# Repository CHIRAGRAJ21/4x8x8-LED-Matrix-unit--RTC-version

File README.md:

# 4x8x8-LED-Matrix-Unit (RTC version)
 A wholly designed KiCad based project featuring a 4x8x8 LED Matrix unit, which for this particular variation is developed to function as a real time clock; hold four 8x8 LED matrix displays controlled by an Arduino Pro mini. The board also includes two push buttons to which you can assign arbitrary functions. This board also features a connector for USB to TTL Serial Adapter Module for Arduino Mini Port USB to Serial Interface Module CYT1007 and a connector for DS3231 IIC Precision RTC, such that every time arduino need not to be detached from the board for uploading of a new program or updating the former employing an external bridging device.

# FINISHED and ASSEMBLED PCB

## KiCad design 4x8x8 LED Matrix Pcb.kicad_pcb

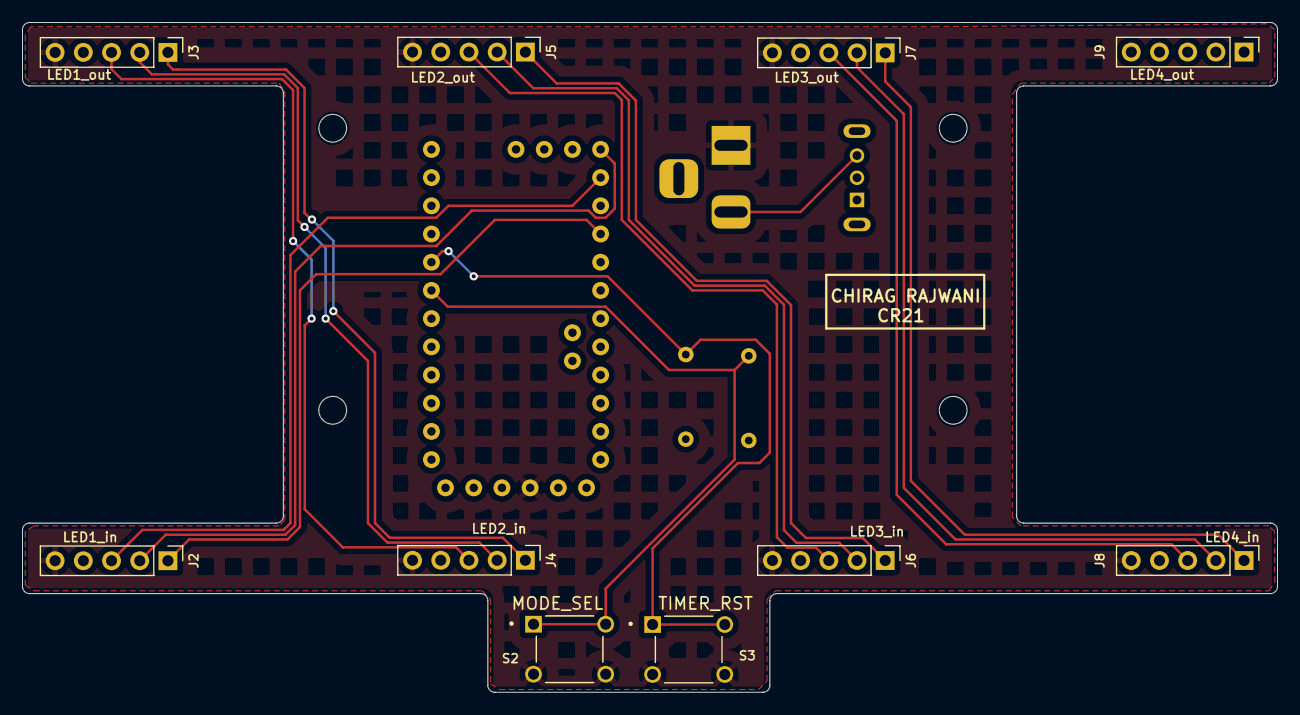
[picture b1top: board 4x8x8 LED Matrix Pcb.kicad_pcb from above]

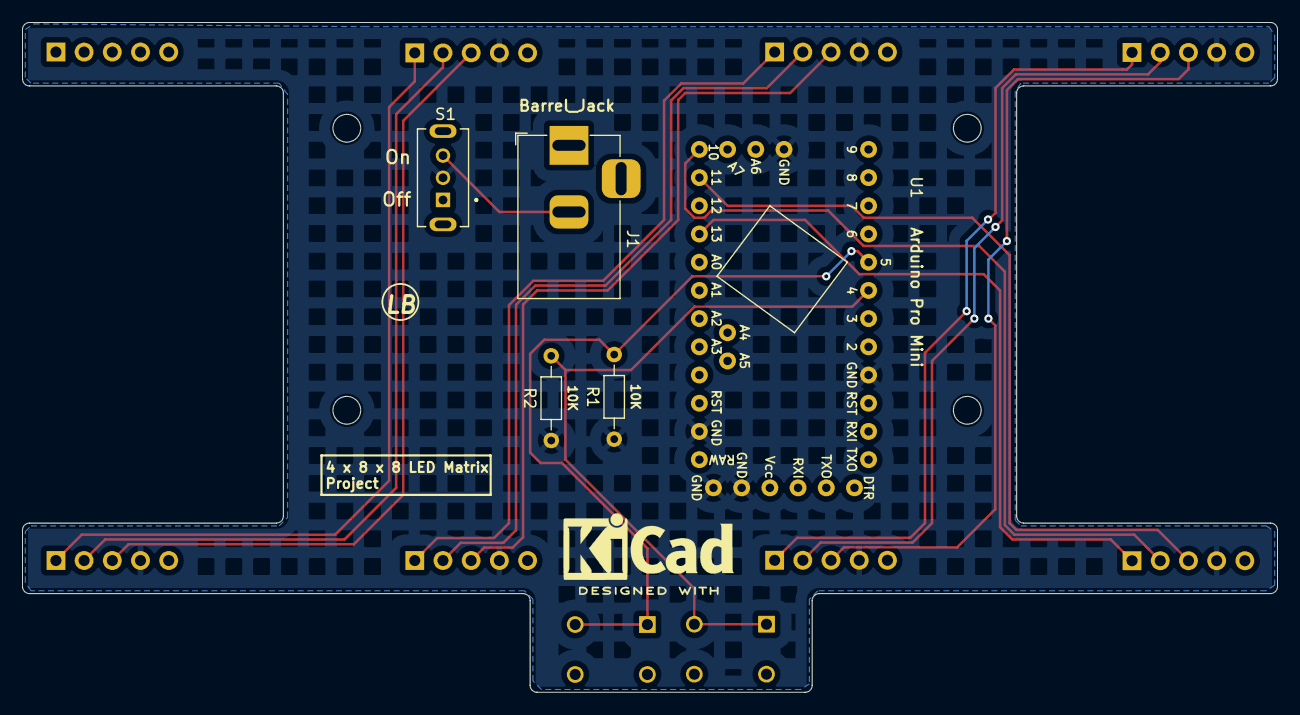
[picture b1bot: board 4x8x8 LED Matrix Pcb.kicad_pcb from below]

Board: 2 copper layers, 113.0 x 60.3 mm, 19 parts (5 on the bottom side), 17 nets.

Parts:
H1, H2, H3, H4: MountingHole; MountingHole_2.5mm
J1: Barrel_Jack; BarrelJack_Horizontal
J2: LED1_in; PinHeader_1x05_P2.54mm_Vertical
J3: LED1_out; PinHeader_1x05_P2.54mm_Vertical
J4: LED2_in; PinHeader_1x05_P2.54mm_Vertical
J5: LED2_out; PinHeader_1x05_P2.54mm_Vertical
J6: LED3_in; PinHeader_1x05_P2.54mm_Vertical
J7: LED3_out; PinHeader_1x05_P2.54mm_Vertical
J8: LED4_in; PinHeader_1x05_P2.54mm_Vertical
J9: LED4_out; PinHeader_1x05_P2.54mm_Vertical
R1, R2: 10K; R_Axial_DIN0204_L3.6mm_D1.6mm_P7.62mm_Horizontal
S1: SS12D07VG4; SW_SS12D07VG4
S2, S3: 1825967-1; SW_1825967-1
U1: ArduinoProMini; ArduinoProMiniCustom

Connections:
/CLK0: J2.1, U1.18 (13)
/CLK1: J3.1, J4.1
/CLK2: J5.1, J6.1
/CLK3: J7.1, J8.1
/CS0: J2.2, U1.15 (10)
/CS1: J3.2, J4.2
/CS2: J5.2, J6.2
/CS3: J7.2, J8.2
/DIN0: J2.3, U1.16 (11)
/DIN1: J3.3, J4.3
/DIN2: J5.3, J6.3
/DIN3: J7.3, J8.3
/MODE_SEL: R2.2, S2.1, S2.2, U1.6 (4)
/TIMER_RST: R1.2, S3.1, S3.2, U1.7 (5)
/Vcc: J1.1, J2.5, J3.5, J4.5, J5.5, J6.5, J7.5, J8.5, S2.3, S2.4, S3.3, S3.4, U1.29 (Vcc)
GND: J2.4, J3.4, J4.4, J5.4, J6.4, J7.4, J8.4, R1.1, R2.1, S1.2, U1.3 (GND), U1.12 (GND), U1.25 (GND), U1.27 (GND), U1.28 (GND)
unnamed: J1.2, S1.3
